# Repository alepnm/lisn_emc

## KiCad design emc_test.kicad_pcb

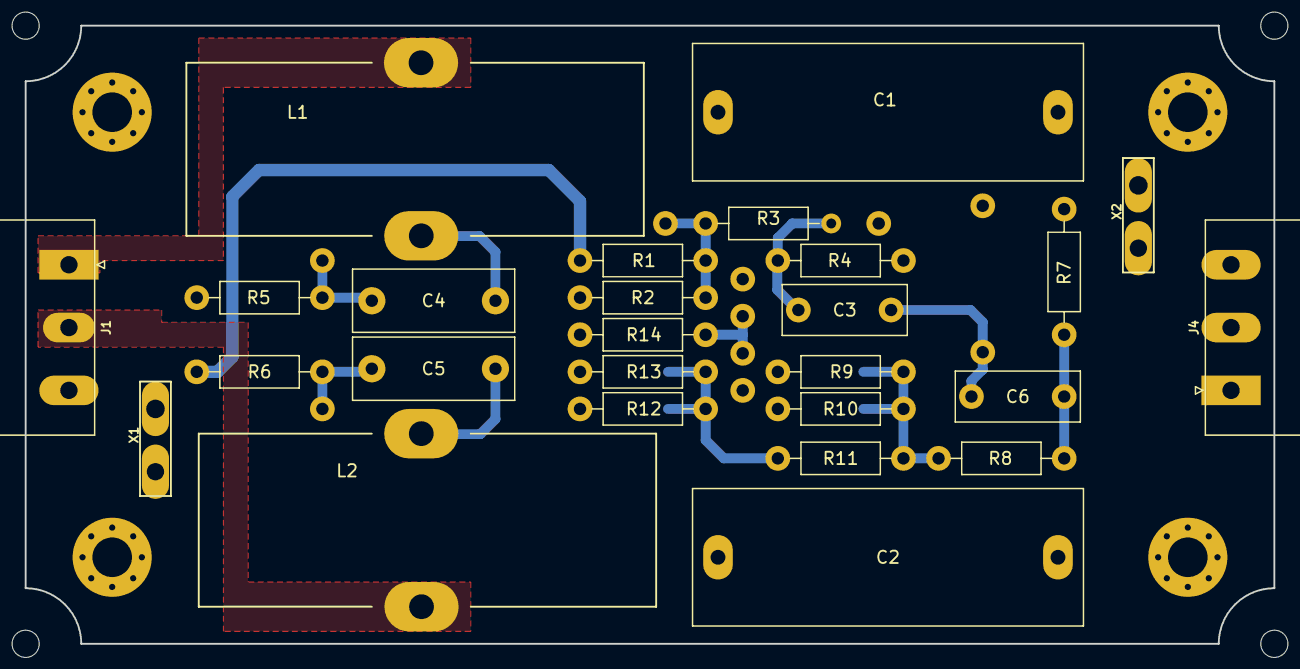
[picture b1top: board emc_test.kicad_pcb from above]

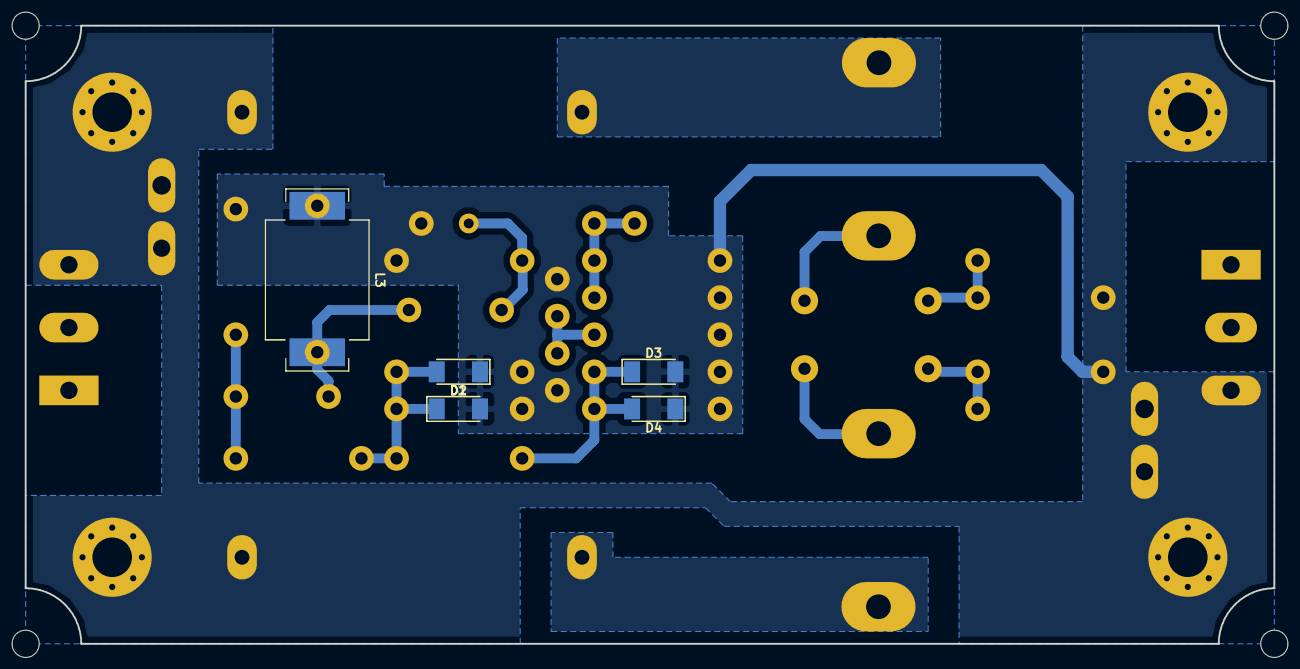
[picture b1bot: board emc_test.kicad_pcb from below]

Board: 2 copper layers, 101.0 x 50.0 mm, 31 parts (5 on the bottom side), 13 nets.

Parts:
C1, C2: 1.0uF; C_Rect_L31.5mm_W11.0mm_P27.50mm_MKS4
C3, C6: 0.47uF; C_Rect_L10.0mm_W4.0mm_P7.50mm_MKS4
C4, C5: 0.1uF; C_Rect_L13.0mm_W5.0mm_P10.00mm_FKS3_FKP3_MKS4
D1, D2, D3, D4: BAS32; D_MiniMELF
J1, J4: MSTBA_3C_5.08_Angled; PhoenixContact_MSTBA-G_03x5.08mm_Angled
L1, L2: 50uH/10A; Choke_Toroid_12x38mm_Vertical
L3: 1mH; L_Neosid_Ms85T_mod
R1: 620; R_Axial_DIN0207_L6.3mm_D2.5mm_P10.16mm_Horizontal
R2: 560; R_Axial_DIN0207_L6.3mm_D2.5mm_P10.16mm_Horizontal
R3: 18; R_Axial_DIN0207_L6.3mm_D2.5mm_P10.16mm_Horizontal
R4, R7: 220; R_Axial_DIN0207_L6.3mm_D2.5mm_P10.16mm_Horizontal
R5, R6: 100k; R_Axial_DIN0207_L6.3mm_D2.5mm_P10.16mm_Horizontal
R8: 30; R_Axial_DIN0207_L6.3mm_D2.5mm_P10.16mm_Horizontal
R9: 240; R_Axial_DIN0207_L6.3mm_D2.5mm_P10.16mm_Horizontal
R10: 270; R_Axial_DIN0207_L6.3mm_D2.5mm_P10.16mm_Horizontal
R11: 12; R_Axial_DIN0207_L6.3mm_D2.5mm_P10.16mm_Horizontal
R12: 820; R_Axial_DIN0207_L6.3mm_D2.5mm_P10.16mm_Horizontal
R13: 910; R_Axial_DIN0207_L6.3mm_D2.5mm_P10.16mm_Horizontal
R14: 910R; R_Axial_DIN0207_L6.3mm_D2.5mm_P10.16mm_Horizontal
X1, X2: PE; Faston_6.3x0.8x14

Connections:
/LINE: C1.1, J1.1, L1.1
/LOUT: C4.1, J4.2, L1.2
/NEU: C2.2, J1.2, L2.1
/NOUT: C5.2, J4.1, L2.2
Earth: C1.2, C2.1, D1.2, D2.1, D3.2, D4.1, J1.3, J4.3, L3.1, R1.1, R2.1, R4.1, R5.1, R6.2, R7.1, R9.1, R10.1, R12.1, R13.1, R14.1, X1.1, X2.1
unnamed: C3.1, R3.2, R4.2
unnamed: C3.2, C6.1, L3.2
unnamed: C4.2, R5.2
unnamed: C5.1, R6.1
unnamed: C6.2, R7.2, R8.1
unnamed: D1.1, D2.2, R8.2, R9.2, R10.2, R11.1
unnamed: D3.1, D4.2, R11.2, R12.2, R13.2
unnamed: R1.2, R2.2, R3.1

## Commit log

2018-01-24 inicializacija
2018-01-24 lisn schemos ir plokstes paruosimas
2018-01-24 plokstes paruosimas
2018-01-25 smulkus pataisymai
2018-02-01 tarpinis kommitas
2018-02-01 .gitignore failas
2018-02-01 Set theme jekyll-theme-time-machine
